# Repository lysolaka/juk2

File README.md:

# JUK2

JUK2 is a CNC plotter firmware for the ESP32-S3 on a custom PCB and plotter frame.

JUK2 is the successor of JUK - a private, messy and ugly project. The project's second version is supposed to be everything the first one was not able to be.

See the file `REFERENCE.md` for usage information.

# Hardware

The custom design can be found under the `juk-pcb` directory. It also has a schematic and a STEP model available for those, who don't have KiCad installed.

The machine operates in Cartesian coordinates using four motors: one for X and Y axes each, and two for the Z axis. The X axis is realized as a moving table, the Y axis is being moved up and down by the Z axis. The X and Y assemblies operate using a belt pulley, the Z axis moves the Y axis assembly using trapezoidal screws from both ends of the axis (hence the need for two motors).

# Software

Just like the first edition of JUK, the entire software stack is developed using Rust. This time the project is split into crates in a single workspace. The structure is as follows:
- `juk-cmd`: command parsing and wire protocol library
- `juk-com`: a communication library implementing text and binary interfaces
- `juk-firmware`: the main firmware executable
- `juk-interp`: movement interpolators library
- `juk-led`: a simple library to use an RGB LED using PWM
- `juk-motion`: motion profiles library

## Toolchain

Building this project requires the Xtensa Rust Toolchain, detailed installation instructions can be found [here](https://docs.espressif.com/projects/rust/book/getting-started/toolchain.html). Additionaly the [espflash](https://github.com/esp-rs/espflash/tree/main/espflash) utility is needed to flash the program onto the board.

# License

All code and design files in this repository are licensed under the GPL-3 license.

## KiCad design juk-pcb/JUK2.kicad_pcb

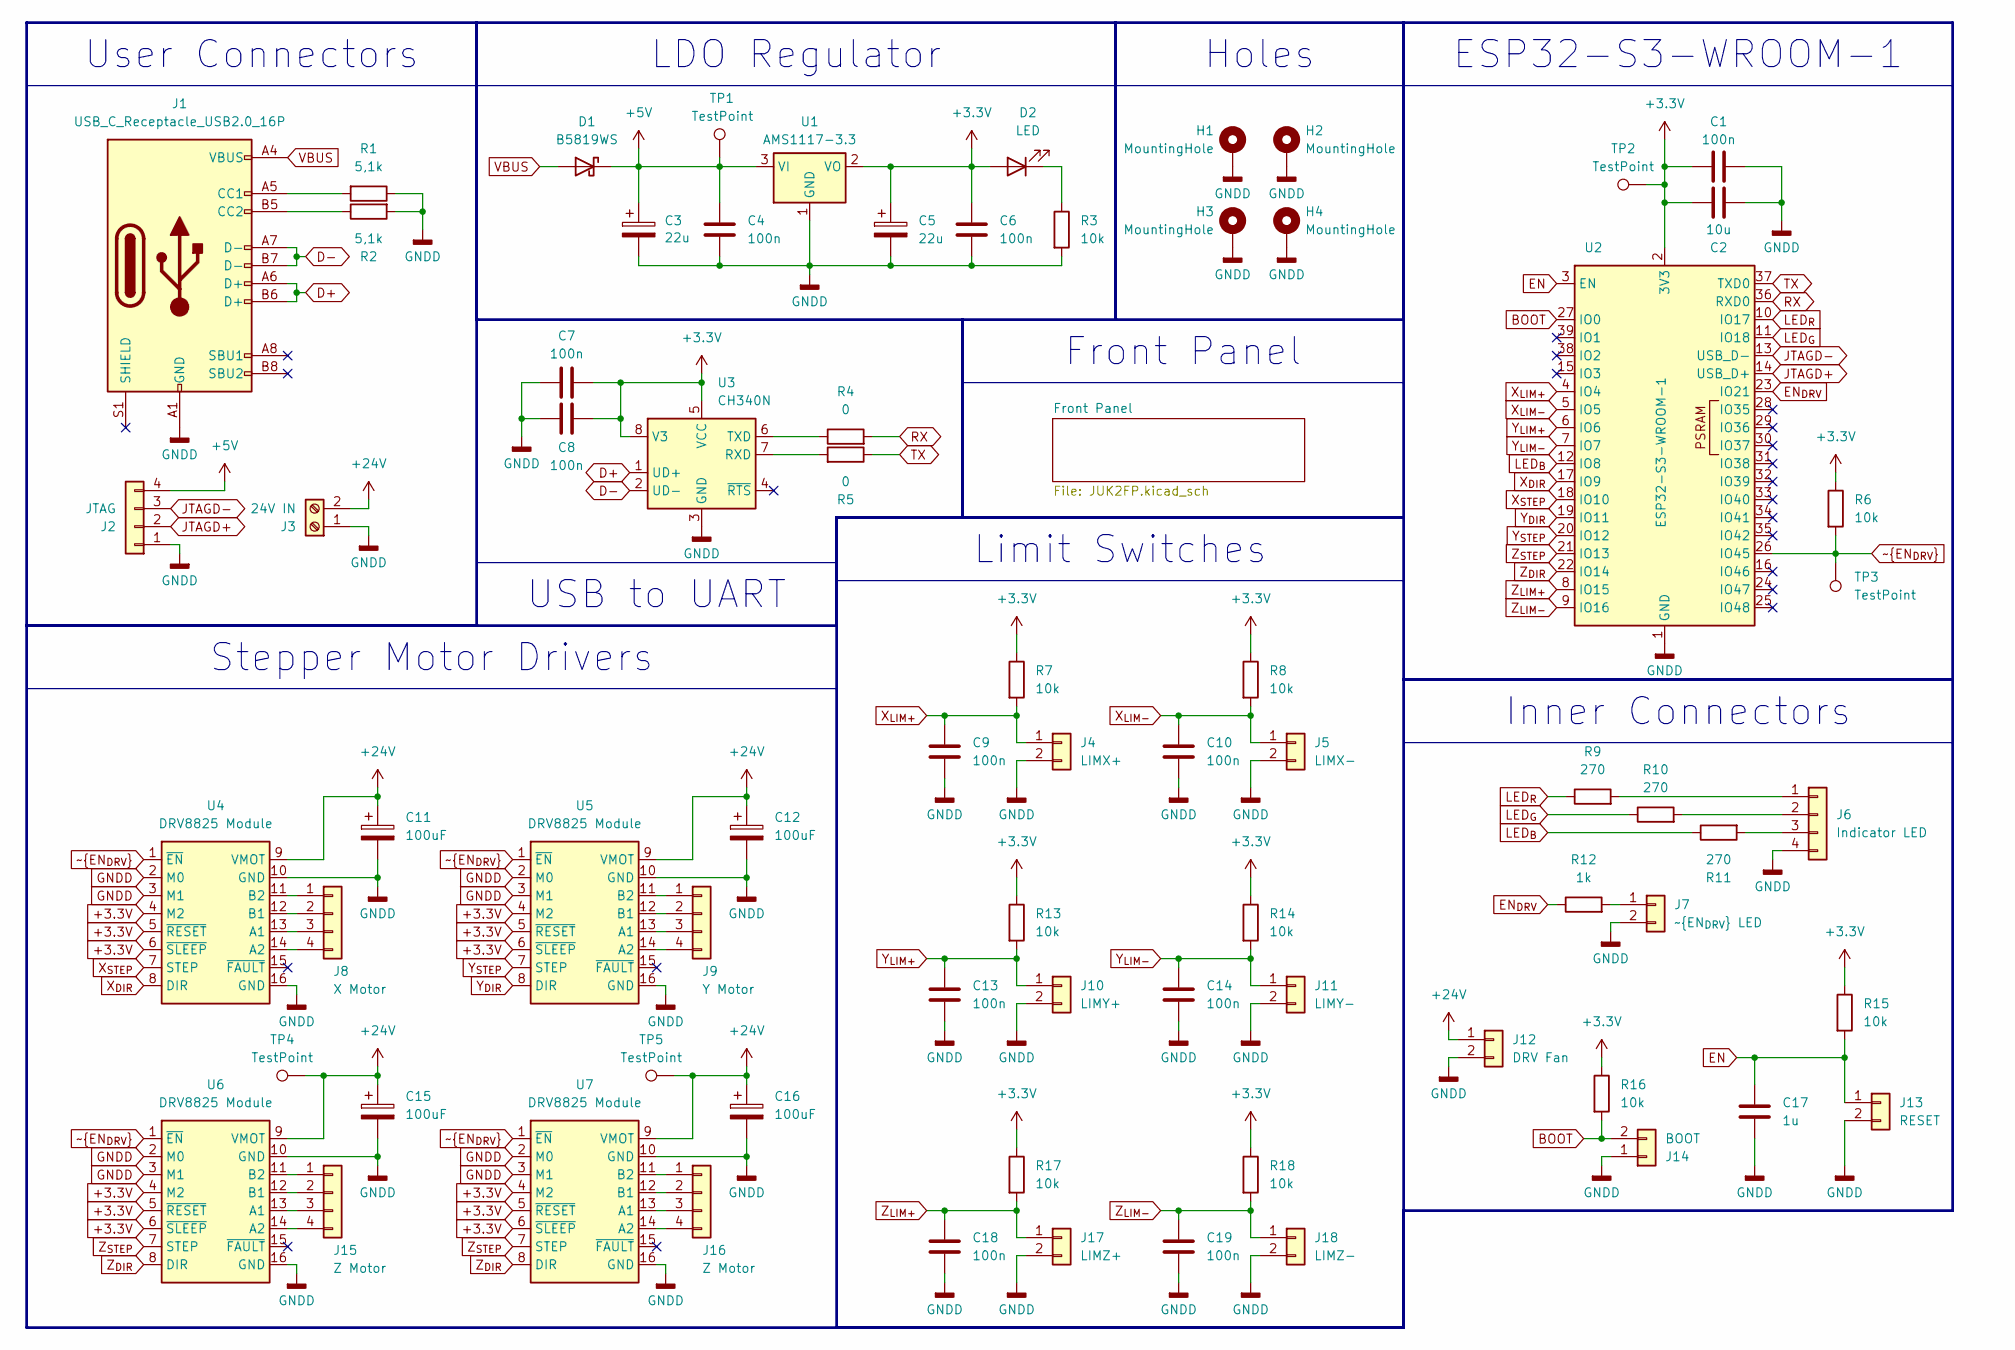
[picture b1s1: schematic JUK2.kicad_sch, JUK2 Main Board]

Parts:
C1, C4, C6, C7, C8, C9, C10, C13, C14, C18, C19: 100n; C_0603_1608Metric_Pad1.08x0.95mm_HandSolder
C2: 10u; C_0603_1608Metric_Pad1.08x0.95mm_HandSolder
C3, C5: 22u; CP_EIA-3528-15_AVX-H_HandSolder
C11, C12, C15, C16: 100uF; CP_Radial_D8.0mm_P3.50mm
C17: 1u; C_0603_1608Metric_Pad1.08x0.95mm_HandSolder
D1: B5819WS; D_SOD-323_HandSoldering
D2: LED; D_0603_1608Metric_Pad1.05x0.95mm_HandSolder
H1, H2, H3, H4: MountingHole; MountingHole_3.2mm_M3_Pad
J1: USB_C_Receptacle_USB2.0_16P; USB_C_GCT_USB4085
J2: JTAG; JTAGConnector
J3: 24V IN; TerminalBlock
J4: LIMX+; 2PinConnector
J5: LIMX-; 2PinConnector
J6: Indicator LED; 4PinConnector
J7: ~{EN_{DRV}} LED; 2PinConnector
J8: X Motor; MotorConnector
J9: Y Motor; MotorConnector
J10: LIMY+; 2PinConnector
J11: LIMY-; 2PinConnector
J12: DRV Fan; 2PinConnector
J13: RESET; 2PinConnector
J14: BOOT; PinHeader_1x02_P2.54mm_Vertical
J15, J16: Z Motor; MotorConnector
J17: LIMZ+; 2PinConnector
J18: LIMZ-; 2PinConnector
R1, R2: 5,1k; R_0603_1608Metric_Pad0.98x0.95mm_HandSolder
R3, R6, R7, R8, R13, R14, R15, R16, R17, R18: 10k; R_0603_1608Metric_Pad0.98x0.95mm_HandSolder
R4, R5: 0; R_0805_2012Metric_Pad1.20x1.40mm_HandSolder
R9, R10, R11: 270; R_0603_1608Metric_Pad0.98x0.95mm_HandSolder
R12: 1k; R_0603_1608Metric_Pad0.98x0.95mm_HandSolder
TP1, TP2, TP3, TP4, TP5: TestPoint; TestPoint_Pad_D2.0mm
U1: AMS1117-3.3; SOT-223-3_TabPin2
U2: ESP32-S3-WROOM-1
U3: CH340N; JEITA_SOIC-8_3.9x4.9mm_P1.27mm
U4, U5, U6, U7: DRV8825 Module; DRV8825_Module

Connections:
+3.3V: C1.1, C2.2, C5.1, C6.1, C7.2, C8.2, D2.2 (A), R6.1, R7.1, R8.1, R13.1, R14.1, R15.1, R16.1, R17.1, R18.1, TP2.1, U1.2 (VO), U2.2 (3V3), U3.5 (VCC), U3.8 (V3), U4.4 (M2), U4.5 (~RESET), U4.6 (~SLEEP), U5.4 (M2), U5.5 (~RESET), U5.6 (~SLEEP), U6.4 (M2), U6.5 (~RESET), U6.6 (~SLEEP), U7.4 (M2), U7.5 (~RESET), U7.6 (~SLEEP)
+5V: C3.1, C4.1, D1.1 (K), J2.4, TP1.1, U1.3 (VI)
+24V: C11.1, C12.1, C15.1, C16.1, J3.2, J12.1, TP4.1, TP5.1, U4.9 (VMOT), U5.9 (VMOT), U6.9 (VMOT), U7.9 (VMOT)
BOOT: J14.2, R16.2, U2.27 (IO0)
D+: J1.A6 (D+), J1.B6 (D+), U3.1 (UD+)
D-: J1.A7 (D-), J1.B7 (D-), U3.2 (UD-)
EN: C17.1, J13.1, R15.2, U2.3 (EN)
EN_{DRV}: R12.1, U2.23 (IO21)
GNDD: C1.2, C2.1, C3.2, C4.2, C5.2, C6.2, C7.1, C8.1, C9.2, C10.2, C11.2, C12.2, C13.2, C14.2, C15.2, C16.2, C17.2, C18.2, C19.2, H1.1, H2.1, H3.1, H4.1, J1.A1 (GND), J1.A12 (GND), J1.B1 (GND), J1.B12 (GND), J2.1, J3.1, J4.2, J5.2, J6.4, J7.2, J10.2, J11.2, J12.2, J13.2, J14.1, J17.2, J18.2, R1.1, R2.2, R3.2, U1.1 (GND), U2.1 (GND), U2.40 (GND), U2.41 (GND), U3.3 (GND), U4.2 (M0), U4.3 (M1), U4.10 (GND), U4.16 (GND), U5.2 (M0), U5.3 (M1), U5.10 (GND), U5.16 (GND), U6.2 (M0), U6.3 (M1), U6.10 (GND), U6.16 (GND), U7.2 (M0), U7.3 (M1), U7.10 (GND), U7.16 (GND)
JTAGD+: J2.2, U2.14 (USB_D+)
JTAGD-: J2.3, U2.13 (USB_D-)
LED_{B}: R11.1, U2.12 (IO8)
LED_{G}: R10.1, U2.11 (IO18)
LED_{R}: R9.1, U2.10 (IO17)
unnamed: D2.1 (K), R3.1
unnamed: J1.A5 (CC1), R1.2
unnamed: J1.B5 (CC2), R2.1
unnamed: J6.1, R9.2
unnamed: J6.2, R10.2
unnamed: J6.3, R11.2
unnamed: J7.1, R12.2
unnamed: J8.1, U4.11 (B2)
unnamed: J8.2, U4.12 (B1)
unnamed: J8.3, U4.13 (A1)
unnamed: J8.4, U4.14 (A2)
unnamed: J9.1, U5.11 (B2)
unnamed: J9.2, U5.12 (B1)
unnamed: J9.3, U5.13 (A1)
unnamed: J9.4, U5.14 (A2)
unnamed: J15.1, U6.11 (B2)
unnamed: J15.2, U6.12 (B1)
unnamed: J15.3, U6.13 (A1)
unnamed: J15.4, U6.14 (A2)
unnamed: J16.1, U7.11 (B2)
unnamed: J16.2, U7.12 (B1)
unnamed: J16.3, U7.13 (A1)
unnamed: J16.4, U7.14 (A2)
unnamed: R5.2, U3.7 (RXD)
unnamed: R4.1, U3.6 (TXD)
RX: R4.2, U2.36 (RXD0)
TX: R5.1, U2.37 (TXD0)
VBUS: D1.2 (A), J1.A4 (VBUS), J1.A9 (VBUS), J1.B4 (VBUS), J1.B9 (VBUS)
X_{DIR}: U2.17 (IO9), U4.8 (DIR)
X_{LIM+}: C9.1, J4.1, R7.2, U2.4 (IO4)
X_{LIM-}: C10.1, J5.1, R8.2, U2.5 (IO5)
X_{STEP}: U2.18 (IO10), U4.7 (STEP)
Y_{DIR}: U2.19 (IO11), U5.8 (DIR)
Y_{LIM+}: C13.1, J10.1, R13.2, U2.6 (IO6)
Y_{LIM-}: C14.1, J11.1, R14.2, U2.7 (IO7)
Y_{STEP}: U2.20 (IO12), U5.7 (STEP)
Z_{DIR}: U2.22 (IO14), U6.8 (DIR), U7.8 (DIR)
Z_{LIM+}: C18.1, J17.1, R17.2, U2.8 (IO15)
Z_{LIM-}: C19.1, J18.1, R18.2, U2.9 (IO16)
Z_{STEP}: U2.21 (IO13), U6.7 (STEP), U7.7 (STEP)
~EN_{DRV}: R6.2, TP3.1, U2.26 (IO45), U4.1 (~EN), U5.1 (~EN), U6.1 (~EN), U7.1 (~EN)

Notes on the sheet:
ESP32-S3-WROOM-1
Limit Switches
Front Panel
LDO Regulator
Holes
Inner Connectors
USB to UART
Stepper Motor Drivers
User Connectors

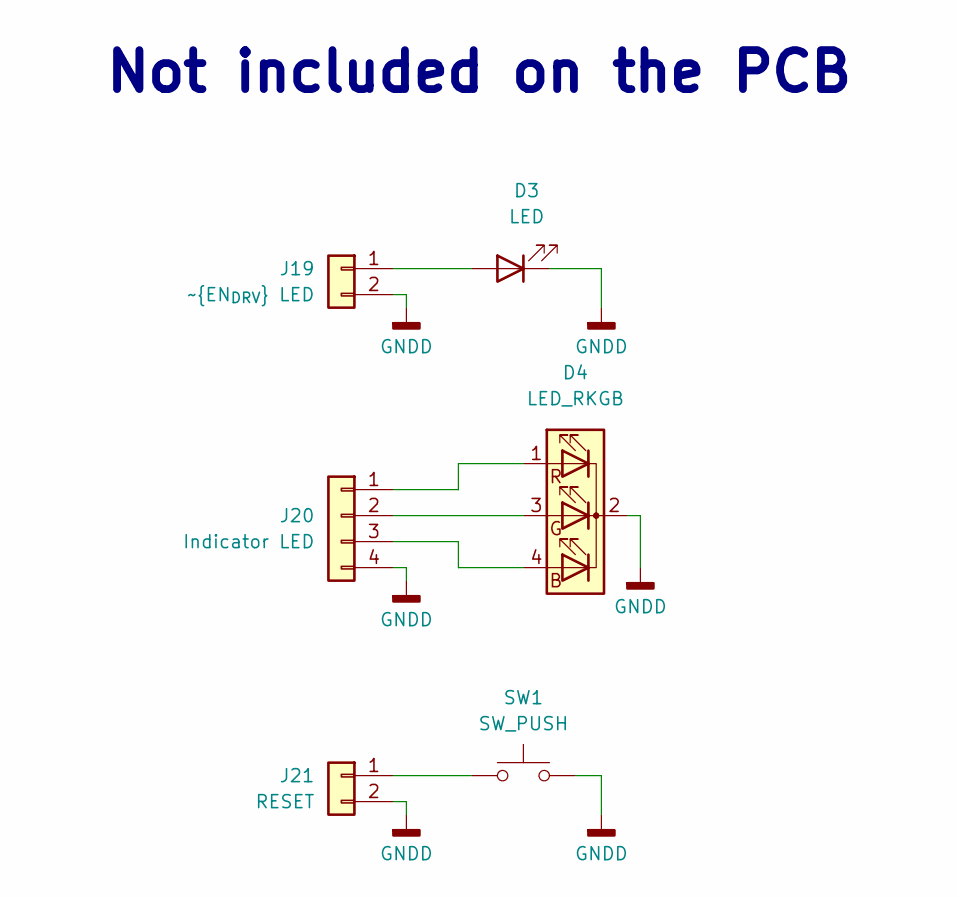
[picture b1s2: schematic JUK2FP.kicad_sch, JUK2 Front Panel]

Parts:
D3: LED; LED_D5.0mm
D4: LED_RKGB; LED_D5.0mm-4_RKGB
J19: ~{EN_{DRV}} LED; 2PinConnector
J20: Indicator LED; 4PinConnector
J21: RESET; 2PinConnector
SW1: SW_PUSH; SW_PUSH_6mm_H13mm

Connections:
unnamed: D3.1 (K), D4.2 (K), J19.2, J20.4, J21.2, SW1.2
unnamed: D3.2 (A), J19.1
unnamed: D4.1 (RA), J20.1
unnamed: D4.3 (GA), J20.2
unnamed: D4.4 (BA), J20.3
unnamed: J21.1, SW1.1

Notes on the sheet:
Not included on the PCB

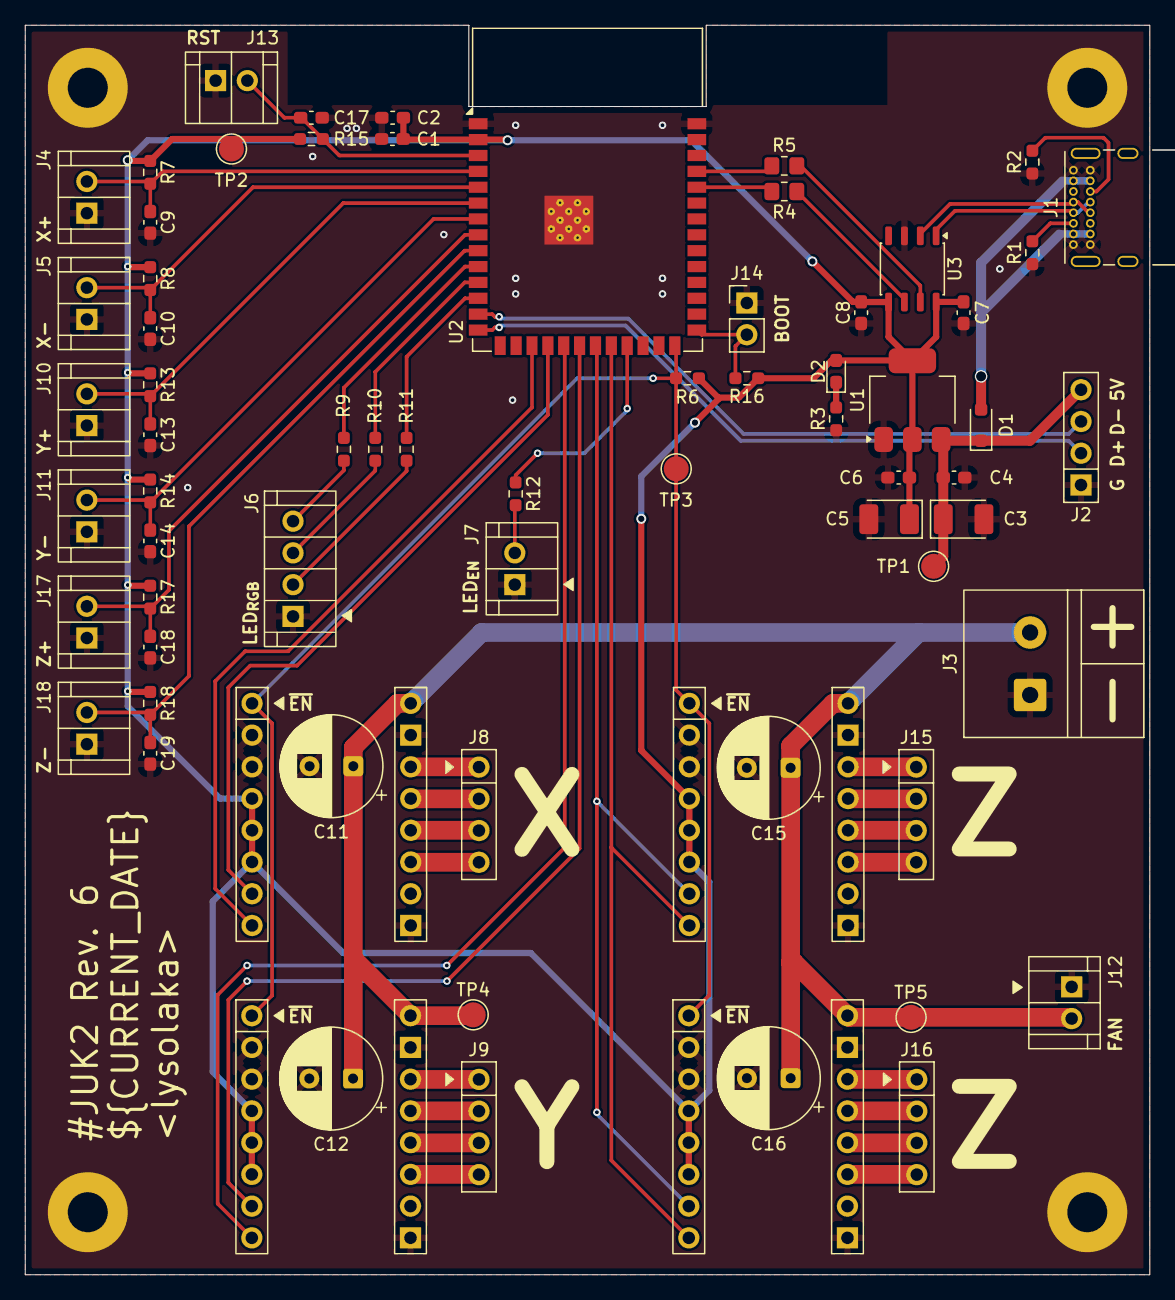
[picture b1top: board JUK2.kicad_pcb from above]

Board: 2 copper layers, 90.0 x 100.0 mm, 73 parts (0 on the bottom side), 55 nets.

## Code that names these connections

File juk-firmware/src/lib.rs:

#![no_std]

extern crate alloc;

pub mod app_core;
pub mod main_core;

pub mod exec;
pub mod global;
pub mod strings;

use esp_hal::peripherals::*;

// to keep the code "clean" we need to define the resources struct again for the sake of making it
// visible to the entire crate, not just the main function

/// Resources struct
pub struct Resources<'d> {
    pub com: ComResources<'d>,
    pub led: LedResources<'d>,
    pub limits: LimitsResources<'d>,
    pub motor: MotorResources<'d>,
}

/// User communication interface resources
pub struct ComResources<'d> {
    pub uart: UART0<'d>,
}

/// RGB indicator LED resources
pub struct LedResources<'d> {
    pub r: GPIO17<'d>,
    pub g: GPIO18<'d>,
    pub b: GPIO8<'d>,
    pub ctrl: LEDC<'d>,
}

/// Limit switches resources
pub struct LimitsResources<'d> {
    pub io: IO_MUX<'d>,
    pub x_p: GPIO4<'d>,
    pub x_m: GPIO5<'d>,
    pub y_p: GPIO6<'d>,
    pub y_m: GPIO7<'d>,
    pub z_p: GPIO15<'d>,
    pub z_m: GPIO16<'d>,
}

/// Motor control resources
pub struct MotorResources<'d> {
    pub tim: TIMG0<'d>,
    pub en_drv: GPIO45<'d>,
    pub en_led: GPIO21<'d>,
    pub x_step: GPIO10<'d>,
    pub x_dir: GPIO9<'d>,
    pub y_step: GPIO12<'d>,
    pub y_dir: GPIO11<'d>,
    pub z_step: GPIO13<'d>,
    pub z_dir: GPIO14<'d>,
}

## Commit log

2026-02-03 chore: init
2026-02-03 feat: implement a driver for the WS2812 LED
2026-02-03 build: cleanup package manifest files
2026-02-09 feat: implement UART echo
2026-02-09 build: add a justfile
2026-02-09 feat: layout for the communication interface
2026-02-09 chore: write a README, add LICENSE
2026-02-11 docs(juk-com): document the `Terminal` trait
2026-02-11 docs(juk-com): document the `eventparser` module
2026-02-11 feat(juk-led): implement `LEDAdapter` in blocking mode
2026-02-11 docs(juk-led): write docs for the `juk-led` library
2026-02-11 docs(juk-com): document the `interface` module
2026-02-11 refactor(juk-com): move the `Terminal` trait to a re-export
2026-02-11 docs(juk-com): document the crate root
2026-02-11 feat(juk-com): implement linebuffer functionality
2026-02-11 feat(juk-com): use the linebuffer in the `Interface`
2026-02-11 feat(juk-com): implement missing helper functions
2026-02-11 feat(juk-firmware): implement a demo for `juk-com`
2026-02-11 fix(juk-com): exit the binary mode with an event to redraw the prompt
2026-02-16 feat(juk-com): implement a history buffer
2026-02-16 feat(juk-com): make pretty status messages
2026-02-16 chore: bump to v0.1.0-dev.2
2026-02-18 feat(juk-firmware): write license and version info strings
2026-02-18 feat(juk-firmware): display license and version info at startup
2026-03-11 build: prettify the justfile
2026-03-30 feat: add a PCB design to the project
2026-03-30 feat!(juk-firmware): remove builtin strings (for now)
2026-03-31 feat(juk-firmware): start both cores and run async executors
2026-03-31 feat(juk-firmware): split resources and cleanly call main for each core
2026-03-31 style: format code, update `rustfmt.toml`
2026-03-31 chore: bump version to `0.1.0-dev.3`
2026-04-02 build: update connection ports, format cargo config
2026-04-02 build: update dependencies
2026-04-02 feat(juk-led): implement a new RGB LED adapter
2026-04-02 feat(juk-firmware): write an example for the LED adapter usage
2026-04-02 feat(juk-led): move logs to the debug level
2026-04-02 chore: bump version to `0.1.0-dev.4`
2026-04-05 chore(juk-motion): library init
2026-04-15 feat(juk-motion): implement math for trapezoidal profiles
2026-04-15 feat(juk-motion): move delay calculation to the `Profile` trait
2026-04-15 docs(juk-motion): document the `Trap` profile
2026-04-15 fix(juk-motion): make the `FastTrap` profile symmetric
2026-04-15 fix(juk-motion): avoid `inf` delays in the `Trap` profile
2026-04-15 build: improve and update the justfile for new hardware
2026-04-15 build: format the justfile
2026-04-19 feat(juk-motion): implement a flat motion profile
2026-04-20 refactor(juk-motion): move motion profiles to a submodule
2026-04-20 feat(juk-motion): implement line and arc interpolators
2026-04-20 feat(juk-motion): add errors and their handling
2026-04-20 chore: bump version to `0.1.0-dev.5`
2026-04-20 chore: regenerate `Cargo.lock`
2026-04-20 docs: update `README.md`
2026-04-20 feat(juk-firmware): reimplement builtin const strings
2026-04-22 refactor: make builtin strings more maintainable
2026-04-22 feat: implement async output on the CLI
2026-04-22 feat(juk-com): implement a help hook for the `?` character
2026-04-22 docs(juk-firmware): document the builting strings
2026-04-22 refactor(juk-motion): rename `ArcDir` to be more mathematical
2026-04-27 docs: start a reference document, document commands
2026-04-27 docs: document the user interface
2026-04-27 docs: document `CTRL + Space` explicitly
2026-04-28 docs: document configuration options
2026-04-28 docs: finalize the reference
2026-05-02 chore(juk-cmd): library init
2026-05-02 feat(juk-cmd): implement the command definitions enum
2026-05-02 feat(juk-cmd): implement command parsing
2026-05-02 docs(juk-cmd): document some items
2026-05-02 feat(juk-cmd): add a movement cancel command
2026-05-03 chore: bump version to `0.1.0-dev.6`
2026-05-03 feat!(juk-firmware): cleanup testing code
2026-05-03 style: format code
2026-05-03 feat(juk-cmd): implement a const constructor for `SystemConfig`
2026-05-03 feat(juk-firmware): implement the LED controller task
2026-05-04 feat(juk-firmware): implement basic terminal functionality
2026-05-05 docs: correct the `CTRL + D` documentation after 8668dfb88235ebabf33229f0f1070c4dc03272fe
2026-05-05 feat(juk-firmware): implement the CLI help hook
2026-05-05 feat(juk-com): make async terminal output binary friendly
2026-05-05 feat(juk-firmware): implement command input hooks
2026-05-06 refactor(juk-firmware): make the prompt a constant string
2026-05-06 feat: implement interface mode switch hook
2026-05-06 feat: implement global tracking of the interface mode
2026-05-06 feat(juk-firmware): add some missing globals
2026-05-06 fix(juk-firmware): flush the queue on the cancel input
2026-05-06 feat: implement config manipulation
2026-05-06 feat(juk-firmware): implement config querying
2026-05-07 fix: make improved error messages for config manipulation reachable
2026-05-07 fix: update the position data type in the reference
2026-05-08 refactor: move types from `juk-motion` to `juk-cmd` to get serialization
2026-05-08 fix: add missing log messages to `set` and `get` executors
2026-05-08 chore: bump version to `0.1.0-dev.7`
2026-05-10 feat(juk-firmware): implement limit switch handling
2026-05-10 feat(juk-firmware): fill in the missing command executors
2026-05-10 feat(juk-cmd): improve ergonomics of conversion to relative displacement
2026-05-10 feat(juk-firmware): improve logging
2026-05-11 feat: implement movement execution
2026-05-11 fix: adjust some parameter limits
2026-05-11 feat(juk-firmware): implement homing execution
2026-05-11 feat(juk-firmware): implement arc movement execution
2026-05-11 chore: bump version to `0.1.0-beta.1`
2026-05-12 fix: cleanup after replacing the shorted capacitor
2026-05-12 feat(juk-firmware): implement error handling for the movement executor
2026-05-12 fix(juk-firmware): correct a typo in logging messages
2026-05-12 feat: improve the `get status` command
2026-05-12 fix(juk-cmd): make homing fail for unknown values of `axis`
2026-05-12 chore: bump version to `0.1.0-beta.2`
2026-05-13 refactor!: move interpolators from juk-motion to juk-interp
2026-05-13 fix(juk-firmware): adjust imports for the juk-interp move
2026-05-13 refactor(juk-cmd)!: improve structure, enable use outside the workspace
2026-05-13 fix: adjust code for the `juk-cmd` refactor
2026-05-13 fix(juk-cmd): export `ParseError` (used in `Displacement`)
2026-05-13 chore: bump version to `0.1.0-beta.3`
2026-05-13 docs: update crate descriptions
2026-05-13 fix(juk-firmware): make homing cancellable
2026-05-14 docs(juk-cmd): update enum variant docs after the refactor
2026-05-15 feat(juk-cmd): `derive(Debug)` when the `export` feature is on
2026-05-15 fix: send async messages in binary mode
2026-05-15 chore: bump version to `0.1.0-beta.4`
2026-05-18 fix(juk-firmware): ignore no-op commands instead of failing
2026-05-18 chore: bump version to `0.1.0`
2026-05-18 docs: add a picture of the machine
2026-05-25 Revert "fix(juk-firmware): ignore no-op commands instead of failing"
    The error handling should be done by the user instead of making the code
    more complicated here.
    This reverts commit a1a5db336c381a9ed70433db7a8571d2cc6799b9.
